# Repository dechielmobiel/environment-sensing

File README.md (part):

# Environment-sensing
this repository contains all the code and hardware designs for a environnmental sensing device that measures environmental paramaters like: illuminance, VOC's, Co2, 11 channel collour, sound, humdidity, temperature and atmospheric pressure, then you can employ tinyML to classify some data with Edge impulse or use a tensorflow model.
# Repesitory contents
- bill of materials 💸
- code 📄
- mechanical drawings 🔧
- pcb files 🔋
# Prerequisites 
# Hardware
- arduino nano 33 ble sense
- esp32 (devkit)
# Software 
- edge impulse cli
- esp idf/arduino ide/visual studio code
- git bash
- nrf connect (Android or IOS)

# Use esp to capture datapoints for edge impulse
first upload the ...data_aquisition code for example (AS7341_data_aquisition) this code can be editted for your specific sensor
then open a commandprompt with edge impulse cli installed and type in the following command.
```
edge-impulse-data-fowarder
```
then the cli will ask you to login to your edge impulse account.
next the cli will ask to wich project you want to connect the device, this can be done by using the arrowkeys.
after this the cli will detect the ammount of sensor axis form the code and asks you to name them sperated by a comma 
(this has to be done in the exact same order as in the code). 

now you can build your impulse 

# deploy the impulse on a esp32 
the code for the deployment of your impulse on esp32 (or other adruino enabled devices) is based on the data forwarder code and can be modified to work with your sensor just as in the aquisition. to change or upgrade the model you only have to change the infernence include.
here is a example of the code for the AS7341.
```
// Include the Arduino library here (something like your_project_inference.h) 
// In the Arduino IDE see **File > Examples > Your project name - Edge Impulse > Static buffer** to get the exact name
#include <zonlicht_vs_kunstlicht_inferencing.h>
#include <Adafruit_AS7341.h>

#define FREQUENCY_HZ        (2)
#define INTERVAL_MS         (1000 / (FREQUENCY_HZ + 1))

Adafruit_AS7341 as7341;
static unsigned long last_interval_ms = 0;
// to classify 1 frame of data you need EI_CLASSIFIER_DSP_INPUT_FRAME_SIZE values
float features[EI_CLASSIFIER_DSP_INPUT_FRAME_SIZE];
// keep track of where we are in the feature array
size_t feature_ix = 0;

void setup() {
    Serial.begin(115200);
    Serial.println("Started");

    if (!as7341.begin()) {
        Serial.println("Failed to initialize AS7341!");
        while (1);
    }
}

void loop() {
    uint16_t readings[12];

    if (millis() > last_interval_ms + INTERVAL_MS) {
        last_interval_ms = millis();

        // read sensor data in exactly the same way as in the Data Forwarder example
         if (!as7341.readAllChannels(readings)){
         Serial.println("Error reading all channels!");
         return;
         }

        // fill the features buffer
        features[feature_ix++] = (readings[0]);
        features[feature_ix++] = (readings[1]);
        features[feature_ix++] = (readings[2]);
        features[feature_ix++] = (readings[3]);
        features[feature_ix++] = (readings[6]);
        features[feature_ix++] = (readings[7]);
        features[feature_ix++] = (readings[8]);
        features[feature_ix++] = (readings[9]);
        features[feature_ix++] = (readings[11]);

        // features buffer full? then classify!
        if (feature_ix == EI_CLASSIFIER_DSP_INPUT_FRAME_SIZE) {
            ei_impulse_result_t result;

            // create signal from features frame
            signal_t signal;
            numpy::signal_from_buffer(features, EI_CLASSIFIER_DSP_INPUT_FRAME_SIZE, &signal);

            // run classifier
            EI_IMPULSE_ERROR res = run_classifier(&signal, &result, false);
            ei_printf("run_classifier returned: %d\n", res);
            if (res != 0) return;

            // print predictions
            ei_printf("Predictions (DSP: %d ms., Classification: %d ms., Anomaly: %d ms.): \n",
                result.timing.dsp, result.timing.classification, result.timing.anomaly);

            // print the predictions
            for (size_t ix = 0; ix < EI_CLASSIFIER_LABEL_COUNT; ix++) {
                ei_printf("%s:\t%.5f\n", result.classification[ix].label, result.classification[ix].value);
            }
        #if EI_CLASSIFIER_HAS_ANOMALY == 1
            ei_printf("anomaly:\t%.3f\n", result.anomaly);
        #endif

            // reset features frame
            feature_ix = 0;
        }
    }
}

void ei_printf(const char *format, ...) {
    static char print_buf[1024] = { 0 };

    va_list args;
    va_start(args, format);
    int r = vsnprintf(print_buf, sizeof(print_buf), format, args);
    va_end(args);

    if (r > 0) {
        Serial.write(print_buf);
    }
}

```
# test the deployment code
to test of the model and code is correct open the static_buffer example in your generated library.
next go to your model for exaple at live classification and load a validated sample and go to detailed results copy the raw feature to paste in the following line of the code:
```arduino
static const float features[] = {
    -19.8800, -0.6900, 8.2300, -17.6600, -1.1300, 5.9700, ...
};
```
after this compare the result of the code to the model and if the same the code is working correctly.

# how to use a Tensorflow Lite model on edge devices.
```Jupyter Notebook

Train a Simple TensorFlow Lite for Microcontrollers model
This notebook demonstrates the process of training a 2.5 kB model using TensorFlow and converting it for use with TensorFlow Lite for Microcontrollers.

Deep learning networks learn to model patterns in underlying data. Here, we're going to train a network to model data generated by a sine function. This will result in a model that can take a value, x, and predict its sine, y.

The model created in this notebook is used in the hello_world example for TensorFlow Lite for MicroControllers.

Run in Google Colab	View source on GitHub
Configure Defaults

# Define paths to model files
import os
MODELS_DIR = 'models/'
if not os.path.exists(MODELS_DIR):
    os.mkdir(MODELS_DIR)
MODEL_TF = MODELS_DIR + 'model'
MODEL_NO_QUANT_TFLITE = MODELS_DIR + 'model_no_quant.tflite'
MODEL_TFLITE = MODELS_DIR + 'model.tflite'
MODEL_TFLITE_MICRO = MODELS_DIR + 'model.cc'
     
Setup Environment
Install Dependencies

! pip install tensorflow==2.4.0
     
Requirement already satisfied: tensorflow==2.4.0rc0 in /usr/local/lib/python3.6/dist-packages (2.4.0rc0)
Requirement already satisfied: termcolor~=1.1.0 in /usr/local/lib/python3.6/dist-packages (from tensorflow==2.4.0rc0) (1.1.0)
Requirement already satisfied: gast==0.3.3 in /usr/local/lib/python3.6/dist-packages (from tensorflow==2.4.0rc0) (0.3.3)
Requirement already satisfied: astunparse~=1.6.3 in /usr/local/lib/python3.6/dist-packages (from tensorflow==2.4.0rc0) (1.6.3)
Requirement already satisfied: absl-py~=0.10 in /usr/local/lib/python3.6/dist-packages (from tensorflow==2.4.0rc0) (0.10.0)
Requirement already satisfied: keras-preprocessing~=1.1.2 in /usr/local/lib/python3.6/dist-packages (from tensorflow==2.4.0rc0) (1.1.2)
Requirement already satisfied: six~=1.15.0 in /usr/local/lib/python3.6/dist-packages (from tensorflow==2.4.0rc0) (1.15.0)
Requirement already satisfied: tensorboard~=2.3 in /usr/local/lib/python3.6/dist-packages (from tensorflow==2.4.0rc0) (2.3.0)
Requirement already satisfied: tensorflow-estimator~=2.3.0 in /usr/local/lib/python3.6/dist-packages (from tensorflow==2.4.0rc0) (2.3.0)
Requirement already satisfied: flatbuffers~=1.12.0 in /usr/local/lib/python3.6/dist-packages (from tensorflow==2.4.0rc0) (1.12)
Requirement already satisfied: google-pasta~=0.2 in /usr/local/lib/python3.6/dist-packages (from tensorflow==2.4.0rc0) (0.2.0)
Requirement already satisfied: protobuf~=3.13.0 in /usr/local/lib/python3.6/dist-packages (from tensorflow==2.4.0rc0) (3.13.0)
Requirement already satisfied: grpcio~=1.32.0 in /usr/local/lib/python3.6/dist-packages (from tensorflow==2.4.0rc0) (1.32.0)
Requirement already satisfied: h5py~=2.10.0 in /usr/local/lib/python3.6/dist-packages (from tensorflow==2.4.0rc0) (2.10.0)
Requirement already satisfied: wrapt~=1.12.1 in /usr/local/lib/python3.6/dist-packages (from tensorflow==2.4.0rc0) (1.12.1)
Requirement already satisfied: opt-einsum~=3.3.0 in /usr/local/lib/python3.6/dist-packages (from tensorflow==2.4.0rc0) (3.3.0)
Requirement already satisfied: numpy~=1.19.2 in /usr/local/lib/python3.6/dist-packages (from tensorflow==2.4.0rc0) (1.19.4)
Requirement already satisfied: typing-extensions~=3.7.4 in /usr/local/lib/python3.6/dist-packages (from tensorflow==2.4.0rc0) (3.7.4.3)
Requirement already satisfied: wheel~=0.35 in /usr/local/lib/python3.6/dist-packages (from tensorflow==2.4.0rc0) (0.35.1)
Requirement already satisfied: werkzeug>=0.11.15 in /usr/local/lib/python3.6/dist-packages (from tensorboard~=2.3->tensorflow==2.4.0rc0) (1.0.1)
Requirement already satisfied: markdown>=2.6.8 in /usr/local/lib/python3.6/dist-packages (from tensorboard~=2.3->tensorflow==2.4.0rc0) (3.3.3)
Requirement already satisfied: google-auth-oauthlib<0.5,>=0.4.1 in /usr/local/lib/python3.6/dist-packages (from tensorboard~=2.3->tensorflow==2.4.0rc0) (0.4.2)
Requirement already satisfied: tensorboard-plugin-wit>=1.6.0 in /usr/local/lib/python3.6/dist-packages (from tensorboard~=2.3->tensorflow==2.4.0rc0) (1.7.0)
Requirement already satisfied: requests<3,>=2.21.0 in /usr/local/lib/python3.6/dist-packages (from tensorboard~=2.3->tensorflow==2.4.0rc0) (2.23.0)
Requirement already satisfied: setuptools>=41.0.0 in /usr/local/lib/python3.6/dist-packages (from tensorboard~=2.3->tensorflow==2.4.0rc0) (50.3.2)
Requirement already satisfied: google-auth<2,>=1.6.3 in /usr/local/lib/python3.6/dist-packages (from tensorboard~=2.3->tensorflow==2.4.0rc0) (1.17.2)
Requirement already satisfied: importlib-metadata; python_version < "3.8" in /usr/local/lib/python3.6/dist-packages (from markdown>=2.6.8->tensorboard~=2.3->tensorflow==2.4.0rc0) (2.0.0)
Requirement already satisfied: requests-oauthlib>=0.7.0 in /usr/local/lib/python3.6/dist-packages (from google-auth-oauthlib<0.5,>=0.4.1->tensorboard~=2.3->tensorflow==2.4.0rc0) (1.3.0)
Requirement already satisfied: certifi>=2017.4.17 in /usr/local/lib/python3.6/dist-packages (from requests<3,>=2.21.0->tensorboard~=2.3->tensorflow==2.4.0rc0) (2020.6.20)
Requirement already satisfied: urllib3!=1.25.0,!=1.25.1,<1.26,>=1.21.1 in /usr/local/lib/python3.6/dist-packages (from requests<3,>=2.21.0->tensorboard~=2.3->tensorflow==2.4.0rc0) (1.24.3)
Requirement already satisfied: chardet<4,>=3.0.2 in /usr/local/lib/python3.6/dist-packages (from requests<3,>=2.21.0->tensorboard~=2.3->tensorflow==2.4.0rc0) (3.0.4)
Requirement already satisfied: idna<3,>=2.5 in /usr/local/lib/python3.6/dist-packages (from requests<3,>=2.21.0->tensorboard~=2.3->tensorflow==2.4.0rc0) (2.10)
Requirement already satisfied: cachetools<5.0,>=2.0.0 in /usr/local/lib/python3.6/dist-packages (from google-auth<2,>=1.6.3->tensorboard~=2.3->tensorflow==2.4.0rc0) (4.1.1)
Requirement already satisfied: rsa<5,>=3.1.4; python_version >= "3" in /usr/local/lib/python3.6/dist-packages (from google-auth<2,>=1.6.3->tensorboard~=2.3->tensorflow==2.4.0rc0) (4.6)
Requirement already satisfied: pyasn1-modules>=0.2.1 in /usr/local/lib/python3.6/dist-packages (from google-auth<2,>=1.6.3->tensorboard~=2.3->tensorflow==2.4.0rc0) (0.2.8)
Requirement already satisfied: zipp>=0.5 in /usr/local/lib/python3.6/dist-packages (from importlib-metadata; python_version < "3.8"->markdown>=2.6.8->tensorboard~=2.3->tensorflow==2.4.0rc0) (3.4.0)
Requirement already satisfied: oauthlib>=3.0.0 in /usr/local/lib/python3.6/dist-packages (from requests-oauthlib>=0.7.0->google-auth-oauthlib<0.5,>=0.4.1->tensorboard~=2.3->tensorflow==2.4.0rc0) (3.1.0)
Requirement already satisfied: pyasn1>=0.1.3 in /usr/local/lib/python3.6/dist-packages (from rsa<5,>=3.1.4; python_version >= "3"->google-auth<2,>=1.6.3->tensorboard~=2.3->tensorflow==2.4.0rc0) (0.4.8)
Import Dependencies

# TensorFlow is an open source machine learning library
import tensorflow as tf

# Keras is TensorFlow's high-level API for deep learning
from tensorflow import keras
# Numpy is a math library
import numpy as np
# Pandas is a data manipulation library 
import pandas as pd
# Matplotlib is a graphing library
import matplotlib.pyplot as plt
# Math is Python's math library
import math

# Set seed for experiment reproducibility
seed = 1
np.random.seed(seed)
tf.random.set_seed(seed)
     
Dataset
1. Generate Data
The code in the following cell will generate a set of random x values, calculate their sine values, and display them on a graph.

# Number of sample datapoints
SAMPLES = 1000

# Generate a uniformly distributed set of random numbers in the range from
# 0 to 2π, which covers a complete sine wave oscillation
x_values = np.random.uniform(
    low=0, high=2*math.pi, size=SAMPLES).astype(np.float32)

# Shuffle the values to guarantee they're not in order
np.random.shuffle(x_values)

# Calculate the corresponding sine values
y_values = np.sin(x_values).astype(np.float32)

# Plot our data. The 'b.' argument tells the library to print blue dots.
plt.plot(x_values, y_values, 'b.')
plt.show()

2. Add Noise
Since it was generated directly by the sine function, our data fits a nice, smooth curve.

However, machine learning models are good at extracting underlying meaning from messy, real world data. To demonstrate this, we can add some noise to our data to approximate something more life-like.

In the following cell, we'll add some random noise to each value, then draw a new graph:

# Add a small random number to each y value
y_values += 0.1 * np.random.randn(*y_values.shape)

# Plot our data
plt.plot(x_values, y_values, 'b.')
plt.show()

3. Split the Data
We now have a noisy dataset that approximates real world data. We'll be using this to train our model.

To evaluate the accuracy of the model we train, we'll need to compare its predictions to real data and check how well they match up. This evaluation happens during training (where it is referred to as validation) and after training (referred to as testing) It's important in both cases that we use fresh data that was not already used to train the model.

The data is split as follows:

Training: 60%
Validation: 20%
Testing: 20%
The following code will split our data and then plots each set as a different color:

# We'll use 60% of our data for training and 20% for testing. The remaining 20%
# will be used for validation. Calculate the indices of each section.
TRAIN_SPLIT =  int(0.6 * SAMPLES)
TEST_SPLIT = int(0.2 * SAMPLES + TRAIN_SPLIT)

# Use np.split to chop our data into three parts.
# The second argument to np.split is an array of indices where the data will be
# split. We provide two indices, so the data will be divided into three chunks.
x_train, x_test, x_validate = np.split(x_values, [TRAIN_SPLIT, TEST_SPLIT])
y_train, y_test, y_validate = np.split(y_values, [TRAIN_SPLIT, TEST_SPLIT])

# Double check that our splits add up correctly
assert (x_train.size + x_validate.size + x_test.size) ==  SAMPLES

# Plot the data in each partition in different colors:
plt.plot(x_train, y_train, 'b.', label="Train")
plt.plot(x_test, y_test, 'r.', label="Test")
plt.plot(x_validate, y_validate, 'y.', label="Validate")
plt.legend()
plt.show()

Training
1. Design the Model
We're going to build a simple neural network model that will take an input value (in this case, x) and use it to predict a numeric output value (the sine of x). This type of problem is called a regression. It will use layers of neurons to attempt to learn any patterns underlying the training data, so it can make predictions.

To begin with, we'll define two layers. The first layer takes a single input (our x value) and runs it through 8 neurons. Based on this input, each neuron will become activated to a certain degree based on its internal state (its weight and bias values). A neuron's degree of activation is expressed as a number.

The activation numbers from our first layer will be fed as inputs to our second layer, which is a single neuron. It will apply its own weights and bias to these inputs and calculate its own activation, which will be output as our y value.

Note: To learn more about how neural networks function, you can explore the Learn TensorFlow codelabs.

The code in the following cell defines our model using Keras, TensorFlow's high-level API for creating deep learning networks. Once the network is defined, we compile it, specifying parameters that determine how it will be trained:

# We'll use Keras to create a simple model architecture
model_1 = tf.keras.Sequential()

# First layer takes a scalar input and feeds it through 8 "neurons". The
# neurons decide whether to activate based on the 'relu' activation function.
model_1.add(keras.layers.Dense(8, activation='relu', input_shape=(1,)))

# Final layer is a single neuron, since we want to output a single value
model_1.add(keras.layers.Dense(1))

# Compile the model using the standard 'adam' optimizer and the mean squared error or 'mse' loss function for regression.
model_1.compile(optimizer='adam', loss='mse', metrics=['mae'])
     
2. Train the Model
Once we've defined the model, we can use our data to train it. Training involves passing an x value into the neural network, checking how far the network's output deviates from the expected y value, and adjusting the neurons' weights and biases so that the output is more likely to be correct the next time.

Training runs this process on the full dataset multiple times, and each full run-through is known as an epoch. The number of epochs to run during training is a parameter we can set.

During each epoch, data is run through the network in multiple batches. Each batch, several pieces of data are passed into the network, producing output values. These outputs' correctness is measured in aggregate and the network's weights and biases are adjusted accordingly, once per batch. The batch size is also a parameter we can set.

The code in the following cell uses the x and y values from our training data to train the model. It runs for 500 epochs, with 64 pieces of data in each batch. We also pass in some data for validation. As you will see when you run the cell, training can take a while to complete:

# Train the model on our training data while validating on our validation set
history_1 = model_1.fit(x_train, y_train, epochs=500, batch_size=64,
                        validation_data=(x_validate, y_validate))
     
Epoch 1/500
10/10 [==============================] - 1s 47ms/step - loss: 0.7289 - mae: 0.7120 - val_loss: 0.6401 - val_mae: 0.6504
Epoch 2/500
10/10 [==============================] - 0s 6ms/step - loss: 0.6329 - mae: 0.6488 - val_loss: 0.5587 - val_mae: 0.6031
Epoch 3/500
10/10 [==============================] - 0s 6ms/step - loss: 0.5201 - mae: 0.5735 - val_loss: 0.5014 - val_mae: 0.5763
Epoch 4/500
10/10 [==============================] - 0s 6ms/step - loss: 0.5057 - mae: 0.5760 - val_loss: 0.4632 - val_mae: 0.5615
Epoch 5/500
10/10 [==============================] - 0s 5ms/step - loss: 0.4502 - mae: 0.5459 - val_loss: 0.4386 - val_mae: 0.5536
Epoch 6/500
10/10 [==============================] - 0s 6ms/step - loss: 0.4168 - mae: 0.5332 - val_loss: 0.4227 - val_mae: 0.5490
Epoch 7/500
10/10 [==============================] - 0s 6ms/step - loss: 0.4211 - mae: 0.5341 - val_loss: 0.4125 - val_mae: 0.5464
Epoch 8/500
10/10 [==============================] - 0s 6ms/step - loss: 0.3988 - mae: 0.5287 - val_loss: 0.4060 - val_mae: 0.5452
Epoch 9/500
10/10 [==============================] - 0s 5ms/step - loss: 0.3901 - mae: 0.5230 - val_loss: 0.4014 - val_mae: 0.5440
Epoch 10/500
10/10 [==============================] - 0s 5ms/step - loss: 0.3804 - mae: 0.5179 - val_loss: 0.3979 - val_mae: 0.5426
Epoch 11/500
10/10 [==============================] - 0s 5ms/step - loss: 0.3695 - mae: 0.5150 - val_loss: 0.3950 - val_mae: 0.5412
Epoch 12/500
10/10 [==============================] - 0s 5ms/step - loss: 0.3856 - mae: 0.5245 - val_loss: 0.3921 - val_mae: 0.5399
Epoch 13/500
10/10 [==============================] - 0s 6ms/step - loss: 0.3744 - mae: 0.5184 - val_loss: 0.3893 - val_mae: 0.5386
Epoch 14/500
10/10 [==============================] - 0s 6ms/step - loss: 0.3749 - mae: 0.5175 - val_loss: 0.3865 - val_mae: 0.5371
Epoch 15/500
10/10 [==============================] - 0s 5ms/step - loss: 0.3467 - mae: 0.4993 - val_loss: 0.3837 - val_mae: 0.5354
Epoch 16/500
10/10 [==============================] - 0s 6ms/step - loss: 0.3736 - mae: 0.5234 - val_loss: 0.3808 - val_mae: 0.5336
Epoch 17/500
10/10 [==============================] - 0s 6ms/step - loss: 0.3655 - mae: 0.5148 - val_loss: 0.3778 - val_mae: 0.5318
Epoch 18/500
10/10 [==============================] - 0s 5ms/step - loss: 0.3558 - mae: 0.5067 - val_loss: 0.3747 - val_mae: 0.5297
Epoch 19/500
10/10 [==============================] - 0s 5ms/step - loss: 0.3343 - mae: 0.4908 - val_loss: 0.3716 - val_mae: 0.5275
Epoch 20/500
10/10 [==============================] - 0s 5ms/step - loss: 0.3742 - mae: 0.5257 - val_loss: 0.3686 - val_mae: 0.5258
Epoch 21/500
10/10 [==============================] - 0s 5ms/step - loss: 0.3296 - mae: 0.4831 - val_loss: 0.3654 - val_mae: 0.5235
Epoch 22/500
10/10 [==============================] - 0s 5ms/step - loss: 0.3432 - mae: 0.4962 - val_loss: 0.3622 - val_mae: 0.5214
Epoch 23/500
10/10 [==============================] - 0s 5ms/step - loss: 0.3397 - mae: 0.4951 - val_loss: 0.3589 - val_mae: 0.5191
Epoch 24/500
10/10 [==============================] - 0s 6ms/step - loss: 0.3229 - mae: 0.4803 - val_loss: 0.3558 - val_mae: 0.5172
Epoch 25/500
10/10 [==============================] - 0s 6ms/step - loss: 0.3562 - mae: 0.5105 - val_loss: 0.3524 - val_mae: 0.5150
Epoch 26/500
10/10 [==============================] - 0s 5ms/step - loss: 0.3458 - mae: 0.5042 - val_loss: 0.3492 - val_mae: 0.5128
Epoch 27/500
10/10 [==============================] - 0s 5ms/step - loss: 0.3163 - mae: 0.4764 - val_loss: 0.3459 - val_mae: 0.5106
Epoch 28/500
10/10 [==============================] - 0s 5ms/step - loss: 0.3441 - mae: 0.5018 - val_loss: 0.3427 - val_mae: 0.5086
Epoch 29/500
10/10 [==============================] - 0s 5ms/step - loss: 0.3062 - mae: 0.4705 - val_loss: 0.3395 - val_mae: 0.5065
Epoch 30/500
10/10 [==============================] - 0s 5ms/step - loss: 0.3202 - mae: 0.4808 - val_loss: 0.3362 - val_mae: 0.5043
Epoch 31/500
10/10 [==============================] - 0s 7ms/step - loss: 0.3313 - mae: 0.4919 - val_loss: 0.3330 - val_mae: 0.5022
Epoch 32/500
10/10 [==============================] - 0s 18ms/step - loss: 0.3028 - mae: 0.4682 - val_loss: 0.3297 - val_mae: 0.4996
Epoch 33/500
10/10 [==============================] - 0s 5ms/step - loss: 0.3056 - mae: 0.4670 - val_loss: 0.3264 - val_mae: 0.4972
Epoch 34/500
10/10 [==============================] - 0s 5ms/step - loss: 0.3203 - mae: 0.4781 - val_loss: 0.3233 - val_mae: 0.4954
Epoch 35/500
10/10 [==============================] - 0s 6ms/step - loss: 0.3256 - mae: 0.4912 - val_loss: 0.3201 - val_mae: 0.4929
Epoch 36/500
10/10 [==============================] - 0s 5ms/step - loss: 0.3079 - mae: 0.4728 - val_loss: 0.3170 - val_mae: 0.4905
Epoch 37/500
10/10 [==============================] - 0s 6ms/step - loss: 0.2969 - mae: 0.4641 - val_loss: 0.3139 - val_mae: 0.4885
Epoch 38/500
10/10 [==============================] - 0s 6ms/step - loss: 0.3043 - mae: 0.4693 - val_loss: 0.3108 - val_mae: 0.4863
Epoch 39/500
10/10 [==============================] - 0s 6ms/step - loss: 0.2902 - mae: 0.4549 - val_loss: 0.3078 - val_mae: 0.4843
Epoch 40/500
10/10 [==============================] - 0s 6ms/step - loss: 0.3003 - mae: 0.4720 - val_loss: 0.3047 - val_mae: 0.4823
Epoch 41/500
10/10 [==============================] - 0s 6ms/step - loss: 0.2970 - mae: 0.4678 - val_loss: 0.3017 - val_mae: 0.4804
Epoch 42/500
10/10 [==============================] - 0s 6ms/step - loss: 0.2903 - mae: 0.4582 - val_loss: 0.2988 - val_mae: 0.4787
Epoch 43/500
10/10 [==============================] - 0s 6ms/step - loss: 0.2853 - mae: 0.4553 - val_loss: 0.2960 - val_mae: 0.4769
Epoch 44/500
10/10 [==============================] - 0s 6ms/step - loss: 0.2910 - mae: 0.4603 - val_loss: 0.2931 - val_mae: 0.4748
Epoch 45/500
10/10 [==============================] - 0s 6ms/step - loss: 0.2819 - mae: 0.4533 - val_loss: 0.2902 - val_mae: 0.4727
Epoch 46/500
10/10 [==============================] - 0s 6ms/step - loss: 0.2744 - mae: 0.4525 - val_loss: 0.2872 - val_mae: 0.4697
Epoch 47/500
10/10 [==============================] - 0s 5ms/step - loss: 0.2707 - mae: 0.4411 - val_loss: 0.2845 - val_mae: 0.4680
Epoch 48/500
10/10 [==============================] - 0s 6ms/step - loss: 0.2641 - mae: 0.4414 - val_loss: 0.2818 - val_mae: 0.4661
Epoch 49/500
10/10 [==============================] - 0s 6ms/step - loss: 0.2642 - mae: 0.4378 - val_loss: 0.2793 - val_mae: 0.4647
Epoch 50/500
10/10 [==============================] - 0s 6ms/step - loss: 0.2603 - mae: 0.4385 - val_loss: 0.2767 - val_mae: 0.4628
Epoch 51/500
10/10 [==============================] - 0s 6ms/step - loss: 0.2684 - mae: 0.4473 - val_loss: 0.2740 - val_mae: 0.4604
Epoch 52/500
10/10 [==============================] - 0s 6ms/step - loss: 0.2539 - mae: 0.4312 - val_loss: 0.2714 - val_mae: 0.4583
Epoch 53/500
10/10 [==============================] - 0s 6ms/step - loss: 0.2621 - mae: 0.4417 - val_loss: 0.2690 - val_mae: 0.4568
Epoch 54/500
10/10 [==============================] - 0s 6ms/step - loss: 0.2556 - mae: 0.4366 - val_loss: 0.2664 - val_mae: 0.4545
Epoch 55/500
10/10 [==============================] - 0s 6ms/step - loss: 0.2524 - mae: 0.4309 - val_loss: 0.2639 - val_mae: 0.4525
Epoch 56/500
10/10 [==============================] - 0s 6ms/step - loss: 0.2555 - mae: 0.4364 - val_loss: 0.2614 - val_mae: 0.4507
Epoch 57/500
10/10 [==============================] - 0s 6ms/step - loss: 0.2483 - mae: 0.4264 - val_loss: 0.2589 - val_mae: 0.4485
Epoch 58/500
10/10 [==============================] - 0s 7ms/step - loss: 0.2403 - mae: 0.4212 - val_loss: 0.2564 - val_mae: 0.4460
Epoch 59/500
10/10 [==============================] - 0s 6ms/step - loss: 0.2462 - mae: 0.4274 - val_loss: 0.2542 - val_mae: 0.4446
Epoch 60/500
10/10 [==============================] - 0s 5ms/step - loss: 0.2364 - mae: 0.4178 - val_loss: 0.2522 - val_mae: 0.4437
Epoch 61/500
10/10 [==============================] - 0s 6ms/step - loss: 0.2409 - mae: 0.4254 - val_loss: 0.2500 - val_mae: 0.4418
Epoch 62/500
10/10 [==============================] - 0s 5ms/step - loss: 0.2338 - mae: 0.4172 - val_loss: 0.2478 - val_mae: 0.4400
Epoch 63/500
10/10 [==============================] - 0s 6ms/step - loss: 0.2283 - mae: 0.4132 - val_loss: 0.2456 - val_mae: 0.4381
Epoch 64/500
10/10 [==============================] - 0s 6ms/step - loss: 0.2438 - mae: 0.4330 - val_loss: 0.2433 - val_mae: 0.4360
Epoch 65/500
10/10 [==============================] - 0s 5ms/step - loss: 0.2169 - mae: 0.4049 - val_loss: 0.2415 - val_mae: 0.4348
Epoch 66/500
10/10 [==============================] - 0s 5ms/step - loss: 0.2208 - mae: 0.4087 - val_loss: 0.2393 - val_mae: 0.4329
Epoch 67/500
10/10 [==============================] - 0s 5ms/step - loss: 0.2440 - mae: 0.4321 - val_loss: 0.2373 - val_mae: 0.4312
Epoch 68/500
10/10 [==============================] - 0s 5ms/step - loss: 0.2250 - mae: 0.4131 - val_loss: 0.2353 - val_mae: 0.4295
Epoch 69/500
10/10 [==============================] - 0s 6ms/step - loss: 0.2222 - mae: 0.4081 - val_loss: 0.2334 - val_mae: 0.4277
Epoch 70/500
10/10 [==============================] - 0s 5ms/step - loss: 0.2245 - mae: 0.4138 - val_loss: 0.2316 - val_mae: 0.4261
Epoch 71/500
10/10 [==============================] - 0s 6ms/step - loss: 0.2132 - mae: 0.3983 - val_loss: 0.2298 - val_mae: 0.4244
Epoch 72/500
10/10 [==============================] - 0s 18ms/step - loss: 0.2232 - mae: 0.4144 - val_loss: 0.2280 - val_mae: 0.4227
Epoch 73/500
10/10 [==============================] - 0s 7ms/step - loss: 0.2077 - mae: 0.3941 - val_loss: 0.2265 - val_mae: 0.4219
Epoch 74/500
10/10 [==============================] - 0s 5ms/step - loss: 0.2116 - mae: 0.3993 - val_loss: 0.2249 - val_mae: 0.4205
Epoch 75/500
10/10 [==============================] - 0s 7ms/step - loss: 0.2227 - mae: 0.4148 - val_loss: 0.2235 - val_mae: 0.4198
Epoch 76/500
10/10 [==============================] - 0s 5ms/step - loss: 0.2026 - mae: 0.3917 - val_loss: 0.2216 - val_mae: 0.4175
Epoch 77/500
10/10 [==============================] - 0s 6ms/step - loss: 0.2083 - mae: 0.3966 - val_loss: 0.2200 - val_mae: 0.4157
Epoch 78/500
10/10 [==============================] - 0s 5ms/step - loss: 0.2055 - mae: 0.3947 - val_loss: 0.2186 - val_mae: 0.4144
Epoch 79/500
10/10 [==============================] - 0s 5ms/step - loss: 0.2069 - mae: 0.3965 - val_loss: 0.2171 - val_mae: 0.4128
Epoch 80/500
10/10 [==============================] - 0s 5ms/step - loss: 0.1983 - mae: 0.3871 - val_loss: 0.2158 - val_mae: 0.4117
Epoch 81/500
10/10 [==============================] - 0s 6ms/step - loss: 0.1994 - mae: 0.3876 - val_loss: 0.2146 - val_mae: 0.4109
Epoch 82/500
10/10 [==============================] - 0s 6ms/step - loss: 0.1971 - mae: 0.3824 - val_loss: 0.2135 - val_mae: 0.4104
Epoch 83/500
10/10 [==============================] - 0s 6ms/step - loss: 0.1965 - mae: 0.3879 - val_loss: 0.2120 - val_mae: 0.4085
Epoch 84/500
10/10 [==============================] - 0s 5ms/step - loss: 0.2006 - mae: 0.3906 - val_loss: 0.2109 - val_mae: 0.4074
Epoch 85/500
10/10 [==============================] - 0s 6ms/step - loss: 0.2048 - mae: 0.3979 - val_loss: 0.2096 - val_mae: 0.4057
Epoch 86/500
10/10 [==============================] - 0s 6ms/step - loss: 0.1932 - mae: 0.3864 - val_loss: 0.2083 - val_mae: 0.4042
Epoch 87/500
10/10 [==============================] - 0s 6ms/step - loss: 0.1916 - mae: 0.3830 - val_loss: 0.2073 - val_mae: 0.4036
Epoch 88/500
10/10 [==============================] - 0s 5ms/step - loss: 0.1984 - mae: 0.3905 - val_loss: 0.2062 - val_mae: 0.4023
Epoch 89/500
10/10 [==============================] - 0s 6ms/step - loss: 0.1939 - mae: 0.3874 - val_loss: 0.2052 - val_mae: 0.4010
Epoch 90/500
10/10 [==============================] - 0s 5ms/step - loss: 0.1902 - mae: 0.3827 - val_loss: 0.2042 - val_mae: 0.4001
Epoch 91/500
10/10 [==============================] - 0s 7ms/step - loss: 0.1888 - mae: 0.3784 - val_loss: 0.2038 - val_mae: 0.4009
Epoch 92/500
10/10 [==============================] - 0s 6ms/step - loss: 0.1927 - mae: 0.3843 - val_loss: 0.2030 - val_mae: 0.4003
Epoch 93/500
10/10 [==============================] - 0s 5ms/step - loss: 0.1851 - mae: 0.3730 - val_loss: 0.2018 - val_mae: 0.3981
Epoch 94/500
10/10 [==============================] - 0s 6ms/step - loss: 0.1984 - mae: 0.3916 - val_loss: 0.2008 - val_mae: 0.3963
Epoch 95/500
10/10 [==============================] - 0s 5ms/step - loss: 0.1851 - mae: 0.3733 - val_loss: 0.2001 - val_mae: 0.3960
Epoch 96/500
10/10 [==============================] - 0s 5ms/step - loss: 0.1881 - mae: 0.3796 - val_loss: 0.1994 - val_mae: 0.3953
Epoch 97/500
10/10 [==============================] - 0s 6ms/step - loss: 0.1859 - mae: 0.3765 - val_loss: 0.1987 - val_mae: 0.3949
Epoch 98/500
10/10 [==============================] - 0s 6ms/step - loss: 0.1822 - mae: 0.3711 - val_loss: 0.1979 - val_mae: 0.3935
Epoch 99/500
10/10 [==============================] - 0s 6ms/step - loss: 0.1886 - mae: 0.3764 - val_loss: 0.1970 - val_mae: 0.3915
Epoch 100/500
10/10 [==============================] - 0s 5ms/step - loss: 0.1878 - mae: 0.3758 - val_loss: 0.1964 - val_mae: 0.3908
Epoch 101/500
10/10 [==============================] - 0s 6ms/step - loss: 0.1769 - mae: 0.3670 - val_loss: 0.1958 - val_mae: 0.3897
Epoch 102/500
10/10 [==============================] - 0s 5ms/step - loss: 0.1832 - mae: 0.3731 - val_loss: 0.1953 - val_mae: 0.3897
Epoch 103/500
10/10 [==============================] - 0s 6ms/step - loss: 0.1827 - mae: 0.3728 - val_loss: 0.1952 - val_mae: 0.3910
Epoch 104/500
10/10 [==============================] - 0s 5ms/step - loss: 0.1867 - mae: 0.3783 - val_loss: 0.1945 - val_mae: 0.3898
Epoch 105/500
10/10 [==============================] - 0s 6ms/step - loss: 0.1813 - mae: 0.3691 - val_loss: 0.1937 - val_mae: 0.3869
Epoch 106/500
10/10 [==============================] - 0s 6ms/step - loss: 0.1715 - mae: 0.3605 - val_loss: 0.1932 - val_mae: 0.3869
Epoch 107/500
10/10 [==============================] - 0s 5ms/step - loss: 0.1800 - mae: 0.3692 - val_loss: 0.1928 - val_mae: 0.3859
Epoch 108/500
10/10 [==============================] - 0s 7ms/step - loss: 0.1884 - mae: 0.3725 - val_loss: 0.1925 - val_mae: 0.3863
Epoch 109/500
10/10 [==============================] - 0s 6ms/step - loss: 0.1777 - mae: 0.3686 - val_loss: 0.1922 - val_mae: 0.3862
Epoch 110/500
10/10 [==============================] - 0s 5ms/step - loss: 0.1801 - mae: 0.3715 - val_loss: 0.1917 - val_mae: 0.3853
Epoch 111/500
10/10 [==============================] - 0s 5ms/step - loss: 0.1794 - mae: 0.3665 - val_loss: 0.1913 - val_mae: 0.3846
Epoch 112/500
10/10 [==============================] - 0s 6ms/step - loss: 0.1811 - mae: 0.3664 - val_loss: 0.1908 - val_mae: 0.3831
Epoch 113/500
10/10 [==============================] - 0s 6ms/step - loss: 0.1821 - mae: 0.3655 - val_loss: 0.1904 - val_mae: 0.3823
Epoch 114/500
10/10 [==============================] - 0s 5ms/step - loss: 0.1755 - mae: 0.3621 - val_loss: 0.1901 - val_mae: 0.3818
Epoch 115/500
10/10 [==============================] - 0s 5ms/step - loss: 0.1718 - mae: 0.3584 - val_loss: 0.1899 - val_mae: 0.3820
Epoch 116/500
10/10 [==============================] - 0s 5ms/step - loss: 0.1684 - mae: 0.3516 - val_loss: 0.1896 - val_mae: 0.3815
Epoch 117/500
10/10 [==============================] - 0s 5ms/step - loss: 0.1760 - mae: 0.3618 - val_loss: 0.1894 - val_mae: 0.3816
Epoch 118/500
10/10 [==============================] - 0s 5ms/step - loss: 0.1748 - mae: 0.3587 - val_loss: 0.1890 - val_mae: 0.3804
Epoch 119/500
10/10 [==============================] - 0s 6ms/step - loss: 0.1749 - mae: 0.3626 - val_loss: 0.1887 - val_mae: 0.3792
Epoch 120/500
10/10 [==============================] - 0s 6ms/step - loss: 0.1620 - mae: 0.3493 - val_loss: 0.1884 - val_mae: 0.3779
Epoch 121/500
10/10 [==============================] - 0s 5ms/step - loss: 0.1720 - mae: 0.3573 - val_loss: 0.1883 - val_mae: 0.3789
Epoch 122/500
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
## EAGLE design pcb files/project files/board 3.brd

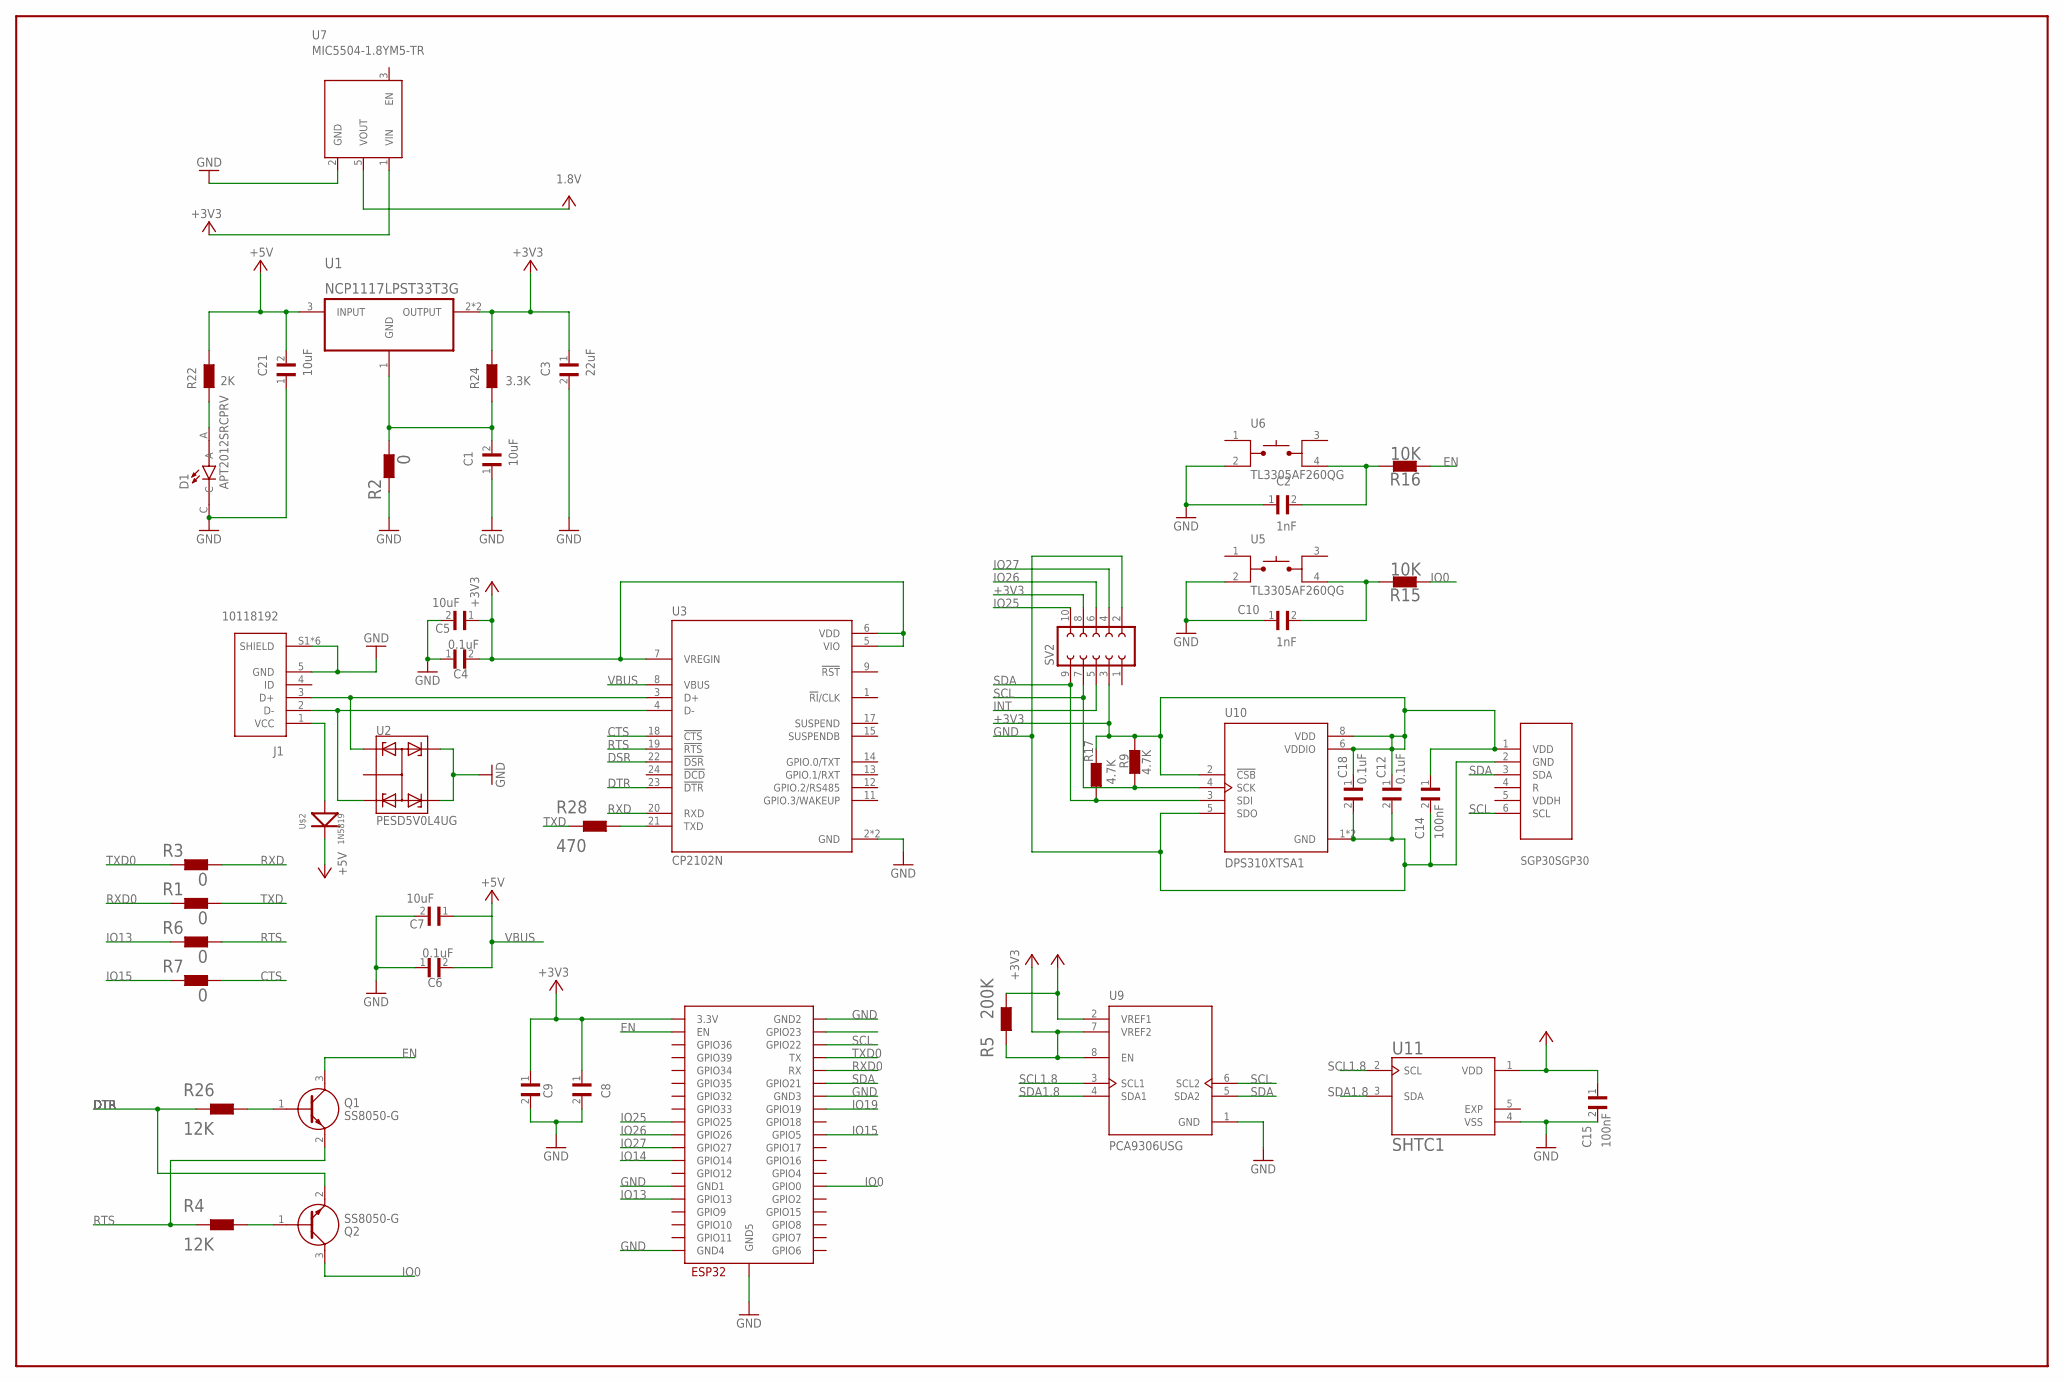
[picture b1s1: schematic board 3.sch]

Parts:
C1, C5, C7, C21: 10uF; CAPC2012X135N
C2, C10: 1nF; CAPC1608X90N
C3: 22uF; CAPC1608X90N
C4, C6, C12, C18: 0.1uF; CAPC1005X55N
C8: CL10A475KQ8NNNC; CAPC1608X90N
C9: 100uF 6.3V 20%; CAPC1608X90N
C14, C15: 100nF; CAPC1608X90N
D1: APT2012SRCPRV; LEDC2012X75N
J1: 10118192; AMPHENOL_10118192-0002LF
Q1, Q2: SS8050-G; SOT95P240X115-3N
R1, R2, R3, R6, R7: 0; RESC0603X26N
R4, R26: 12K; RESC2012X75N
R5: 200K; RESC2012X75N
R9, R17: 4.7K; RESC1608X55N
R15, R16: 10K; RESC2012X70N
R22: 2K; RESC2012X70N
R24: 3.3K; RESC2012X70N
R28: 470; RESC3225X70N
SV2: FE05-2
U1: NCP1117LPST33T3G; SOT230P700X175-4N
U2: PESD5V0L4UG; SOT65P210X110-5N
U3: CP2102N; QFN50P400X400X80-25N
U5, U6: TL3305AF260QG; SW_TL3305AF260QG
U7: MIC5504-1.8YM5-TR; SOT23-5P95_280X145XL45X37N
U9: PCA9306USG; SOP50P310X90-8N
U10: DPS310XTSA1; XDCR_DPS310XTSA1
U11: SHTC1; XDCR_SHTC1
U13: SGP30SGP30; SGP30
U$1: ESP32-WROOM
U$2: 1N5819; SOD-123

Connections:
1.8V: U7.5 (VOUT)
+3V3: C3.1, C4.2, C5.1, C8.1, C9.1, C12.1, C14.1, C18.1, R5.1, R9.2, R17.2, R24.2, SV2.3, SV2.8, U1.2 (OUTPUT), U1.4 (OUTPUT), U3.5 (VIO), U3.6 (VDD), U3.7 (VREGIN), U7.1 (VIN), U9.7 (VREF2), U9.8 (EN), U10.2 (!CSB), U10.6 (VDDIO), U10.8 (VDD), U13.1 (VDD), U$1.3V3 (3.3V)
+5V: C21.2, R22.2, U1.3 (INPUT), U$2.K
CTS: R7.2, U3.18 (!CTS)
DSR: U3.22 (!DSR)
DTR: Q2.2 (E), R26.1, U3.23 (!DTR)
EN: Q1.3 (C), R16.1, U$1.EN
GND: C1.1, C2.1, C3.2, C4.1, C5.2, C6.1, C7.2, C8.2, C9.2, C10.1, C12.2, C14.2, C15.2, C18.2, C21.1, D1.C, J1.5 (GND), J1.S1 (SHIELD), J1.S2 (SHIELD), J1.S3 (SHIELD), J1.S4 (SHIELD), J1.S5 (SHIELD), J1.S6 (SHIELD), R2.1, SV2.2, U2.4, U2.5, U3.2 (GND), U3.25 (GND), U5.2, U6.2, U7.2 (GND), U9.1 (GND), U10.1 (GND), U10.5 (SDO), U10.7 (GND), U11.4 (VSS), U13.2 (GND), U$1.GND1, U$1.GND2, U$1.GND3, U$1.GND4, U$1.GND5
INT: SV2.5
IO0: Q2.3 (C), R15.1, U$1.IO0 (GPIO0)
IO13: R6.1, U$1.IO13 (GPIO13)
IO14: U$1.IO14 (GPIO14)
IO15: R7.1, U$1.IO5 (GPIO5)
IO19: U$1.IO19 (GPIO19)
IO25: SV2.10, U$1.IO25 (GPIO25)
IO26: SV2.6, U$1.IO26 (GPIO26)
IO27: SV2.4, U$1.IO27 (GPIO27)
unnamed: J1.2 (D-), U2.3, U3.4 (D-)
unnamed: J1.3 (D+), U2.1, U3.3 (D+)
unnamed: J1.1 (VCC), U$2.A
unnamed: R28.2, U3.21 (TXD)
unnamed: D1.A, R22.1
unnamed: C1.2, R2.2, R24.1, U1.1 (GND)
unnamed: Q1.1 (B), R26.2
unnamed: Q2.1 (B), R4.2
unnamed: C2.2, R16.2, U6.4
unnamed: C10.2, R15.2, U5.4
RTS: Q1.2 (E), R4.1, R6.2, U3.19 (!RTS)
RXD: R3.2, U3.20 (RXD)
RXD0: R1.1, U$1.RX
SCL: R9.1, SV2.7, U9.6 (SCL2), U10.4 (SCK), U13.6 (SCL), U$1.IO22 (GPIO22)
SCL1.8: U9.3 (SCL1), U11.2 (SCL)
SDA: R17.1, SV2.9, U9.5 (SDA2), U10.3 (SDI), U13.3 (SDA), U$1.IO21 (GPIO21)
SDA1.8: U9.4 (SDA1), U11.3 (SDA)
TXD: R1.2, R28.1
TXD0: R3.1, U$1.TX
VBUS: C6.2, C7.1, U3.8 (VBUS)
VCC: C15.1, R5.2, U9.2 (VREF1), U11.1 (VDD)

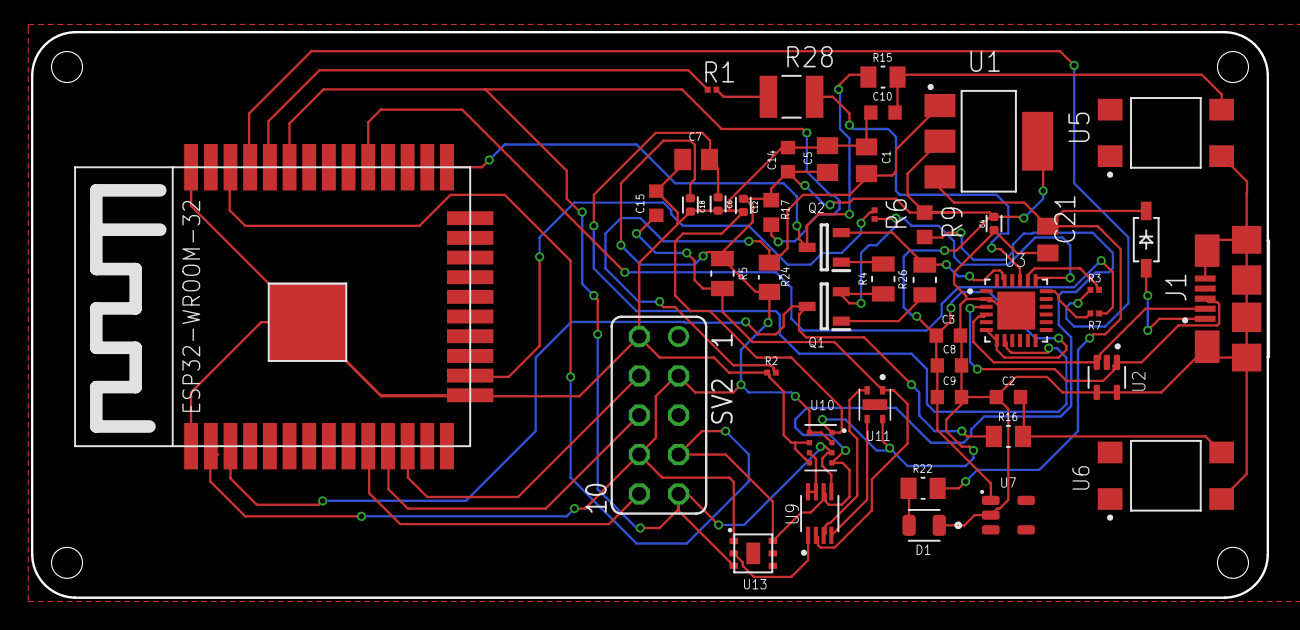
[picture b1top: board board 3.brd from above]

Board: 2 copper layers, 79.8 x 36.5 mm, 47 parts (0 on the bottom side), 33 nets.

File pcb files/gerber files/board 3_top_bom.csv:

Comment;Designator;Footprint;LCSC Part #
0;R1 R2 R3 R6 R7;RESC0603X26N;
0.1uF;C4 C6 C12 C18;CAPC1005X55N;
1N5819;U$2;SOD-123;
1nF;C2 C10;CAPC1608X90N;
2K;R22;RESC2012X70N;
3.3K;R24;RESC2012X70N;
4.7K;R9 R17;RESC1608X55N;
10K;R15 R16;RESC2012X70N;
10uF;C1 C5 C7 C21;CAPC2012X135N;
12K;R4 R26;RESC2012X75N;
22uF;C3;CAPC1608X90N;
100nF;C14 C15;CAPC1608X90N;
100uF 6.3V 20%;C9;CAPC1608X90N;
200K;R5;RESC2012X75N;
470;R28;RESC3225X70N;
10118192;J1;AMPHENOL_10118192-0002LF;
APT2012SRCPRV;D1;LEDC2012X75N;
CL10A475KQ8NNNC;C8;CAPC1608X90N;
CP2102N;U3;QFN50P400X400X80-25N;
DPS310XTSA1;U10;XDCR_DPS310XTSA1;
ESP32-WROOM;U$1;ESP32-WROOM;
MIC5504-1.8YM5-TR;U7;SOT23-5P95_280X145XL45X37N;
NCP1117LPST33T3G;U1;SOT230P700X175-4N;
PCA9306USG;U9;SOP50P310X90-8N;
PESD5V0L4UG;U2;SOT65P210X110-5N;
SGP30SGP30;U13;SGP30;
SHTC1;U11;XDCR_SHTC1;
SS8050-G;Q1 Q2;SOT95P240X115-3N;
TL3305AF260QG;U5 U6;SW_TL3305AF260QG;

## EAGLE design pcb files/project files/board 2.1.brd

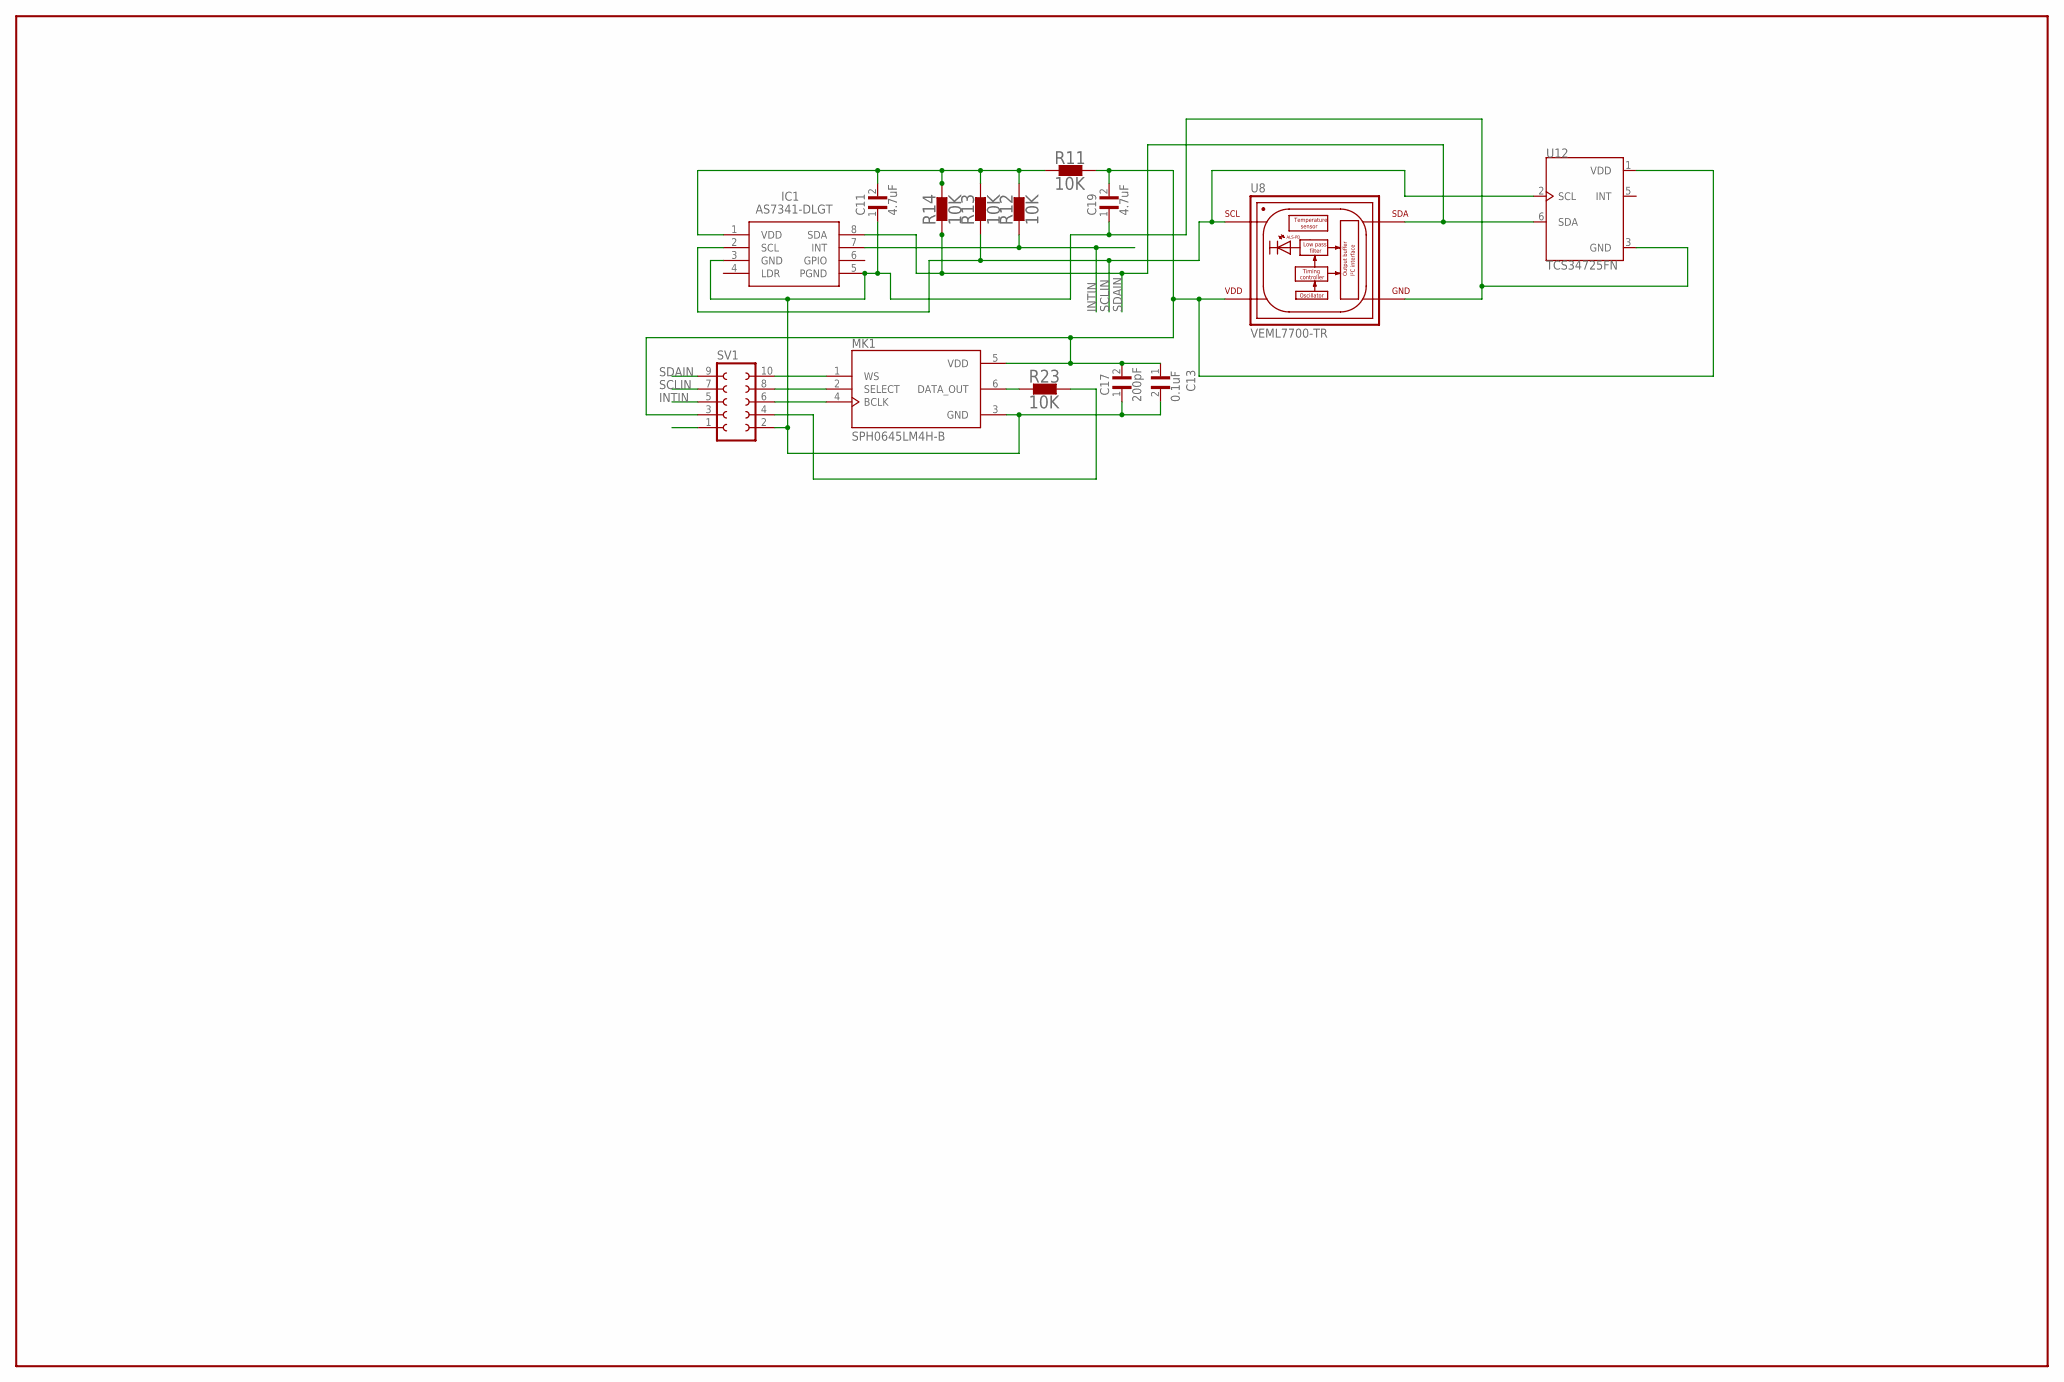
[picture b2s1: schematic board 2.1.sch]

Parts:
C11, C19: 4.7uF; CAPC1608X90N
C13: 0.1uF; CAPC1005X55N
C17: 200pF; CAPC1608X90N
IC1: AS7341-DLGT; AS7341DLGT
MK1: SPH0645LM4H-B; MIC_SPH0645LM4H-B
R11, R12, R13, R14, R23: 10K; RESC2012X70N
SV1: FE05-2
U8: VEML7700-TR; XDCR_VEML7700-TR
U12: TCS34725FN; SON65P200X240X70-6N

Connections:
GND: C11.1, C13.2, C17.1, C19.1, IC1.3 (GND), IC1.5 (PGND), MK1.3 (GND), SV1.2, U8.3 (GND), U12.3 (GND)
INTIN: IC1.7 (INT), R12.1, SV1.5
unnamed: MK1.6 (DATA_OUT), R23.1
unnamed: C13.1, C17.2, C19.2, MK1.5 (VDD), R11.2, SV1.3, U8.2 (VDD), U12.1 (VDD)
unnamed: R23.2, SV1.4
unnamed: MK1.1 (WS), SV1.10
unnamed: MK1.2 (SELECT), SV1.8
unnamed: MK1.4 (BCLK), SV1.6
unnamed: C11.2, IC1.1 (VDD), R11.1, R12.2, R13.2, R14.2
SCLIN: IC1.2 (SCL), R13.1, SV1.7, U8.1 (SCL), U12.2 (SCL)
SDAIN: IC1.8 (SDA), R14.1, SV1.9, U8.4 (SDA), U12.6 (SDA)

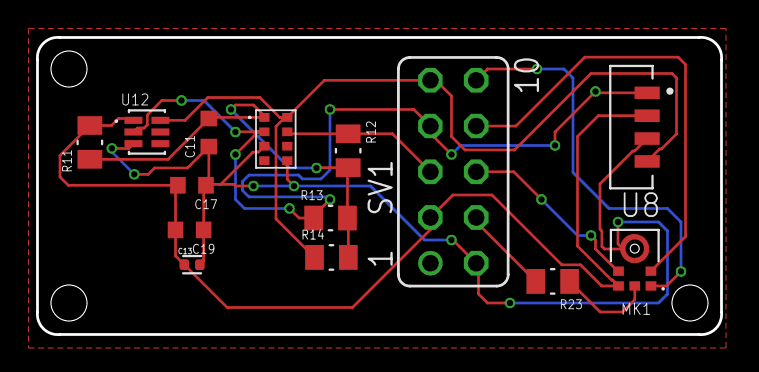
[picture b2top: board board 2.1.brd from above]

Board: 2 copper layers, 38.0 x 16.5 mm, 14 parts (0 on the bottom side), 11 nets.

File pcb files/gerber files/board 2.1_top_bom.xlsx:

Comment | Designator | Footprint | JLCPCB Part #（optional）
0.1uF | C13 | CAPC1005X55N
4.7uF | C11 C19 | CAPC1608X90N
10K | R11 R12 R13 R14 R23 | RESC2012X70N
200pF | C17 | CAPC1608X90N
AS7341-DLGT | IC1 | AS7341DLGT
SPH0645LM4H-B | MK1 | MIC_SPH0645LM4H-B
TCS34725FN | U12 | SON65P200X240X70-6N
VEML7700-TR | U8 | XDCR_VEML7700-TR

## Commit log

2022-12-28 Rename code/edge impulse/model/readme to code/edge impulse/models/readme
2023-02-07 Create Db(a) level
2023-02-07 Create create model
2023-02-07 Create create cpp files
2023-02-07 Create arduino sketch
2023-02-07 Create circadian stimulus
2023-02-07 Rename code/tensorflowlite/readme to code/Tensorflow-Lite/readme
2023-02-08 Rename Db(a) level to Db(a) level (I2S)
2023-02-10 Create how to setup hello world example and convert to C++
2023-02-10 Gemaakt met Colaboratory
2023-02-10 Rename README.md to README.ipynb
2023-02-10 Rename README.ipynb to README.md
2023-02-10 Rename readme (1).md to readme.md
2023-02-12 Rename how to setup hello world example and convert to C++ to how to setup hello world example and convert to C++.ipynb
2023-02-12 Rename readme.ipynb to ESC-50.ipynb
2023-02-12 Rename readme to readme.md
2023-02-21 Create yamnet depploy
